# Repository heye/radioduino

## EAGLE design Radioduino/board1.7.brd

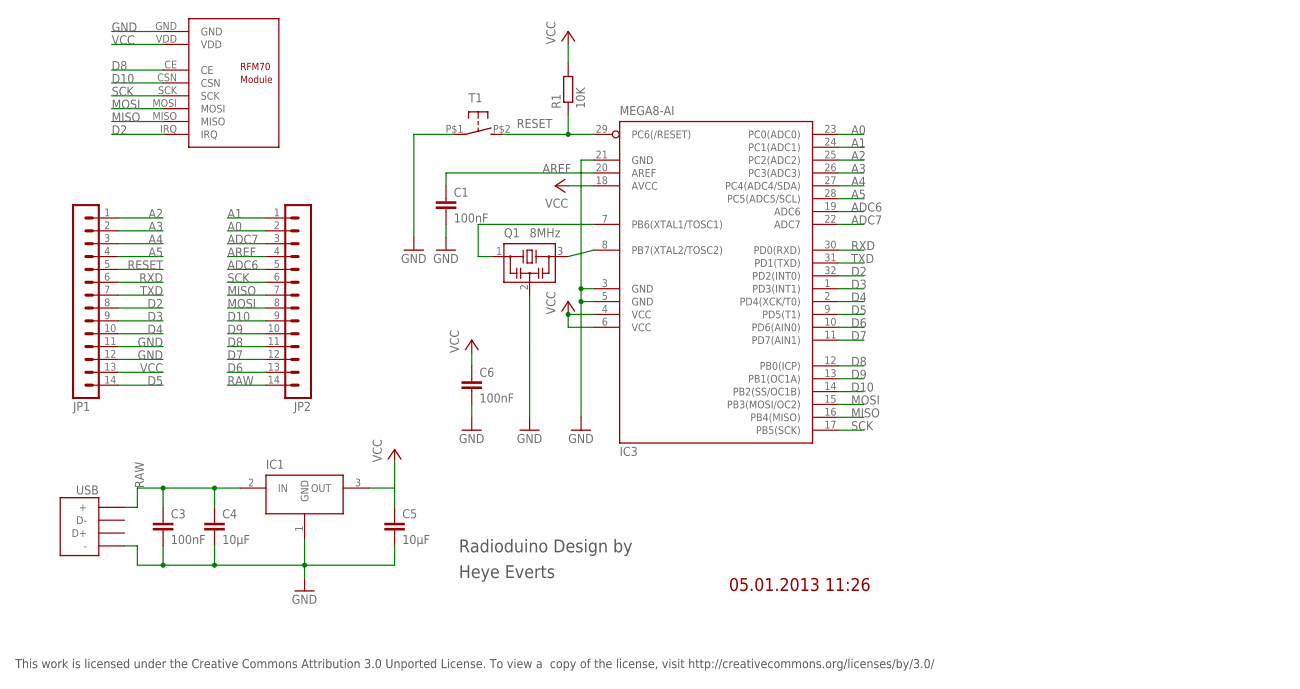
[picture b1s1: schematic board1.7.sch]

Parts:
C1, C3, C6: 100nF; C0603K
C4, C5: 10µF; C0805K
IC1: TS1117CP33; TO252
IC3: MEGA8-AI; TQFP32-08
JP1, JP2: MA14-1
Q1: 8MHz; CSTCE8M00G52
R1: 10K; R0603
RFM70: RFM70
T1: DTSM-3; DTSM31N
USB: USB-MICRO-B-RS

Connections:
A0: IC3.23 (PC0(ADC0)), JP2.2
A1: IC3.24 (PC1(ADC1)), JP2.1
A2: IC3.25 (PC2(ADC2)), JP1.1
A3: IC3.26 (PC3(ADC3)), JP1.2
A4: IC3.27 (PC4(ADC4/SDA)), JP1.3
A5: IC3.28 (PC5(ADC5/SCL)), JP1.4
ADC6: IC3.19 (ADC6), JP2.5
ADC7: IC3.22 (ADC7), JP2.3
AREF: C1.1, IC3.20 (AREF), JP2.4
D2: IC3.32 (PD2(INT0)), JP1.8, RFM70.IRQ
D3: IC3.1 (PD3(INT1)), JP1.9
D4: IC3.2 (PD4(XCK/T0)), JP1.10
D5: IC3.9 (PD5(T1)), JP1.14
D6: IC3.10 (PD6(AIN0)), JP2.13
D7: IC3.11 (PD7(AIN1)), JP2.12
D8: IC3.12 (PB0(ICP)), JP2.11, RFM70.CE
D9: IC3.13 (PB1(OC1A)), JP2.10
D10: IC3.14 (PB2(SS/OC1B)), JP2.9, RFM70.CSN
GND: C1.2, C3.2, C4.2, C5.2, C6.2, IC1.1 (GND), IC3.3 (GND), IC3.5 (GND), IC3.21 (GND), JP1.11, JP1.12, Q1.2, RFM70.GND, T1.P$1, USB.P$5 (-)
MISO: IC3.16 (PB4(MISO)), JP2.7, RFM70.MISO
MOSI: IC3.15 (PB3(MOSI/OC2)), JP2.8, RFM70.MOSI
RAW: C3.1, C4.1, IC1.2 (IN), JP2.14, USB.P$1 (+)
RESET: IC3.29 (PC6(/RESET)), JP1.5, R1.1, T1.P$2 (S)
RXD: IC3.30 (PD0(RXD)), JP1.6
SCK: IC3.17 (PB5(SCK)), JP2.6, RFM70.SCK
TXD: IC3.31 (PD1(TXD)), JP1.7
VCC: C5.1, C6.1, IC1.3 (OUT), IC3.4 (VCC), IC3.6 (VCC), IC3.18 (AVCC), JP1.13, R1.2, RFM70.VDD
XTAL1: IC3.7 (PB6(XTAL1/TOSC1)), Q1.1
XTAL2: IC3.8 (PB7(XTAL2/TOSC2)), Q1.3

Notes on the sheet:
Radioduino Design by
Heye Everts
05.01.2013 11:26
This work is licensed under the Creative Commons Attribution 3.0 Unported License. To view a copy of the license, visit http://creativecommons.org/licenses/by/3.0/

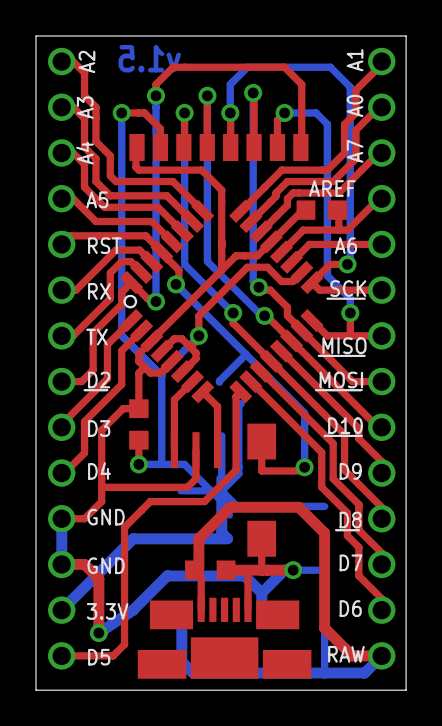
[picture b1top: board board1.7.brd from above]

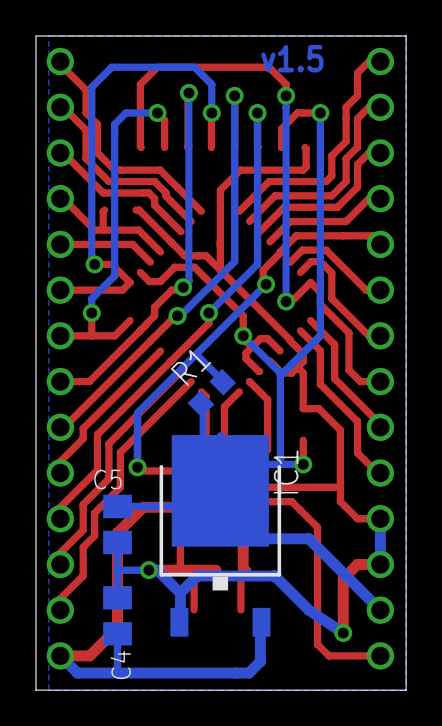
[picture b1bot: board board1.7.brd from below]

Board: 2 copper layers, 20.6 x 36.3 mm, 14 parts (4 on the bottom side), 29 nets.

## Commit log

2013-09-17 added pictures
